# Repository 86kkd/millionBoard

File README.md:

# TODO list

- [x] 电源输入端大电容

- [x] 功率线宽度足够

- [x] 搞懂6pwm和3pwm控制的区别

- [ ] 模拟电路-数字电路去耦合

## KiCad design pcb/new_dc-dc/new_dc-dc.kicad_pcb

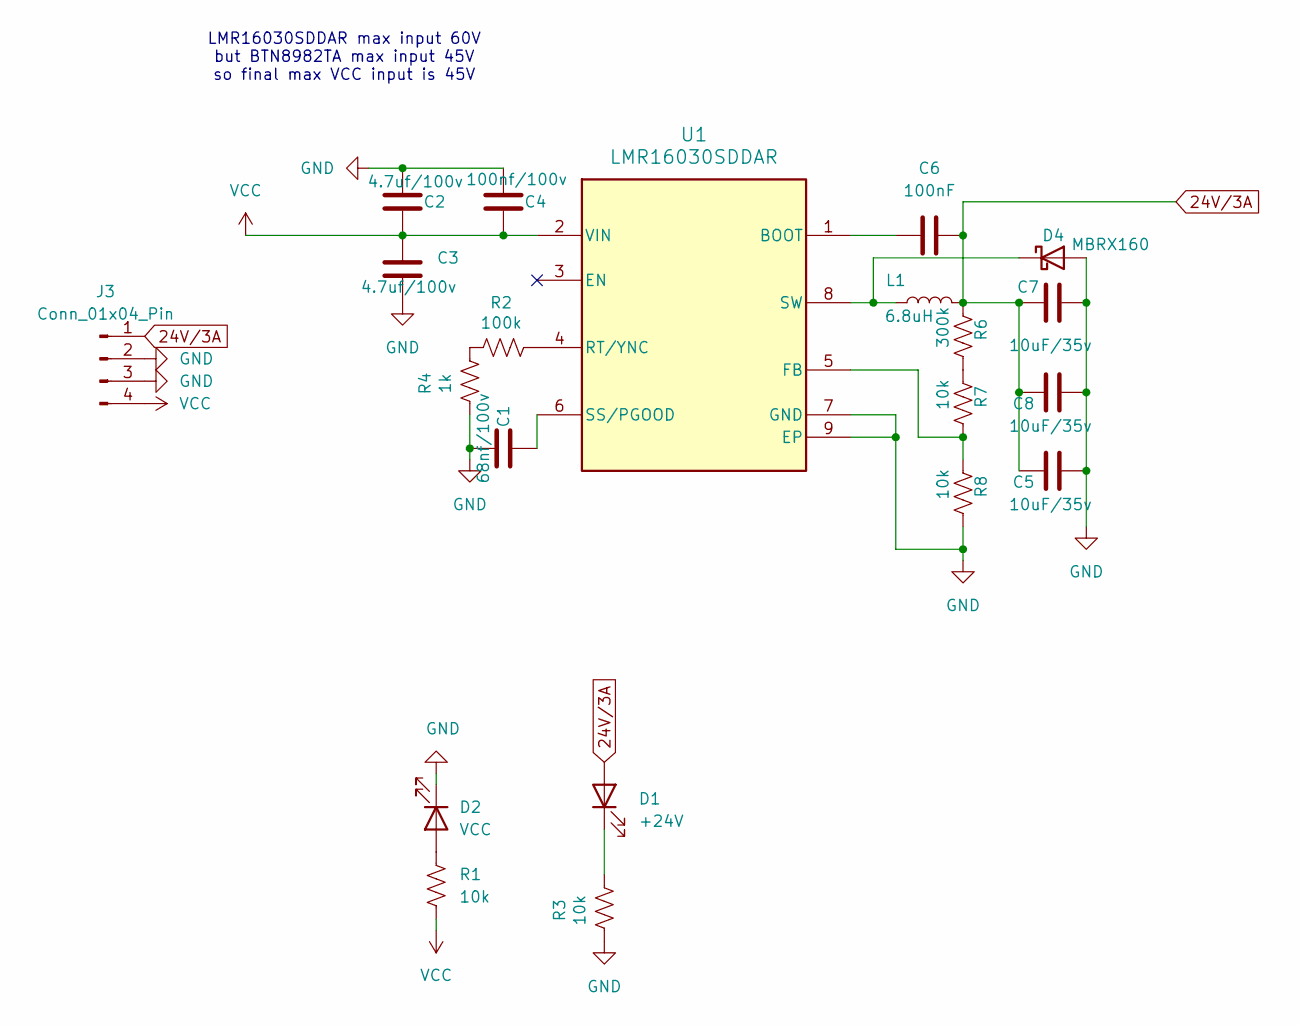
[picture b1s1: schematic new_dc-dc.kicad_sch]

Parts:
C1: 68nf/100v; C_0603_1608Metric
C2, C3: 4.7uf/100v; C_1210_3225Metric
C4: 100nf/100v; C_0603_1608Metric
C5, C7, C8: 10uF/35v; C_1210_3225Metric
C6: 100nF; C_0603_1608Metric
D1: +24V; LED_0603_1608Metric
D2: VCC; LED_0603_1608Metric
D4: MBRX160; D_SOD-123
J3: Conn_01x04_Pin
L1: 6.8uH; L_Chilisin_BMRA00040420
R1, R3, R7, R8: 10k; R_0603_1608Metric
R2: 100k; R_0603_1608Metric
R4: 1k; R_0603_1608Metric
R6: 300k; R_0603_1608Metric
U1: LMR16030SDDAR; TI_SO-PowerPAD-8_ThermalVias

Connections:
24V/3A: C5.2, C6.1, C7.1, C8.2, D1.2 (A), J3.1, L1.2, R6.1
GND: C1.2, C2.2, C3.2, C4.1, C5.1, C7.2, C8.1, D2.1 (K), D4.2 (A), J3.2, J3.3, R3.2, R4.2, R8.2, U1.7 (GND), U1.9 (EP)
unnamed: D1.1 (K), R3.1
unnamed: D2.2 (A), R1.2
unnamed: D4.1 (K), L1.1, U1.8 (SW)
unnamed: R2.2, R4.1
unnamed: R6.2, R7.1
unnamed: C6.2, U1.1 (BOOT)
unnamed: R7.2, R8.1, U1.5 (FB)
unnamed: R2.1, U1.4 (RT/YNC)
unnamed: C1.1, U1.6 (SS/PGOOD)
VCC: C2.1, C3.1, C4.2, J3.4, R1.1, U1.2 (VIN)

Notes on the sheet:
LMR16030SDDAR max input 60V but BTN8982TA max input 45V so final max VCC input is 45V

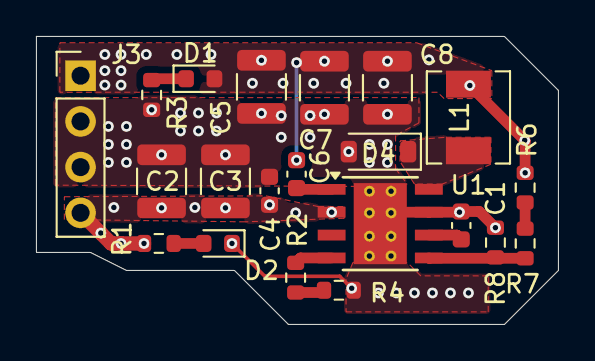
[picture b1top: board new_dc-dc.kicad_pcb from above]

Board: 6 copper layers, 29.0 x 16.0 mm, 21 parts (0 on the bottom side), 12 nets.

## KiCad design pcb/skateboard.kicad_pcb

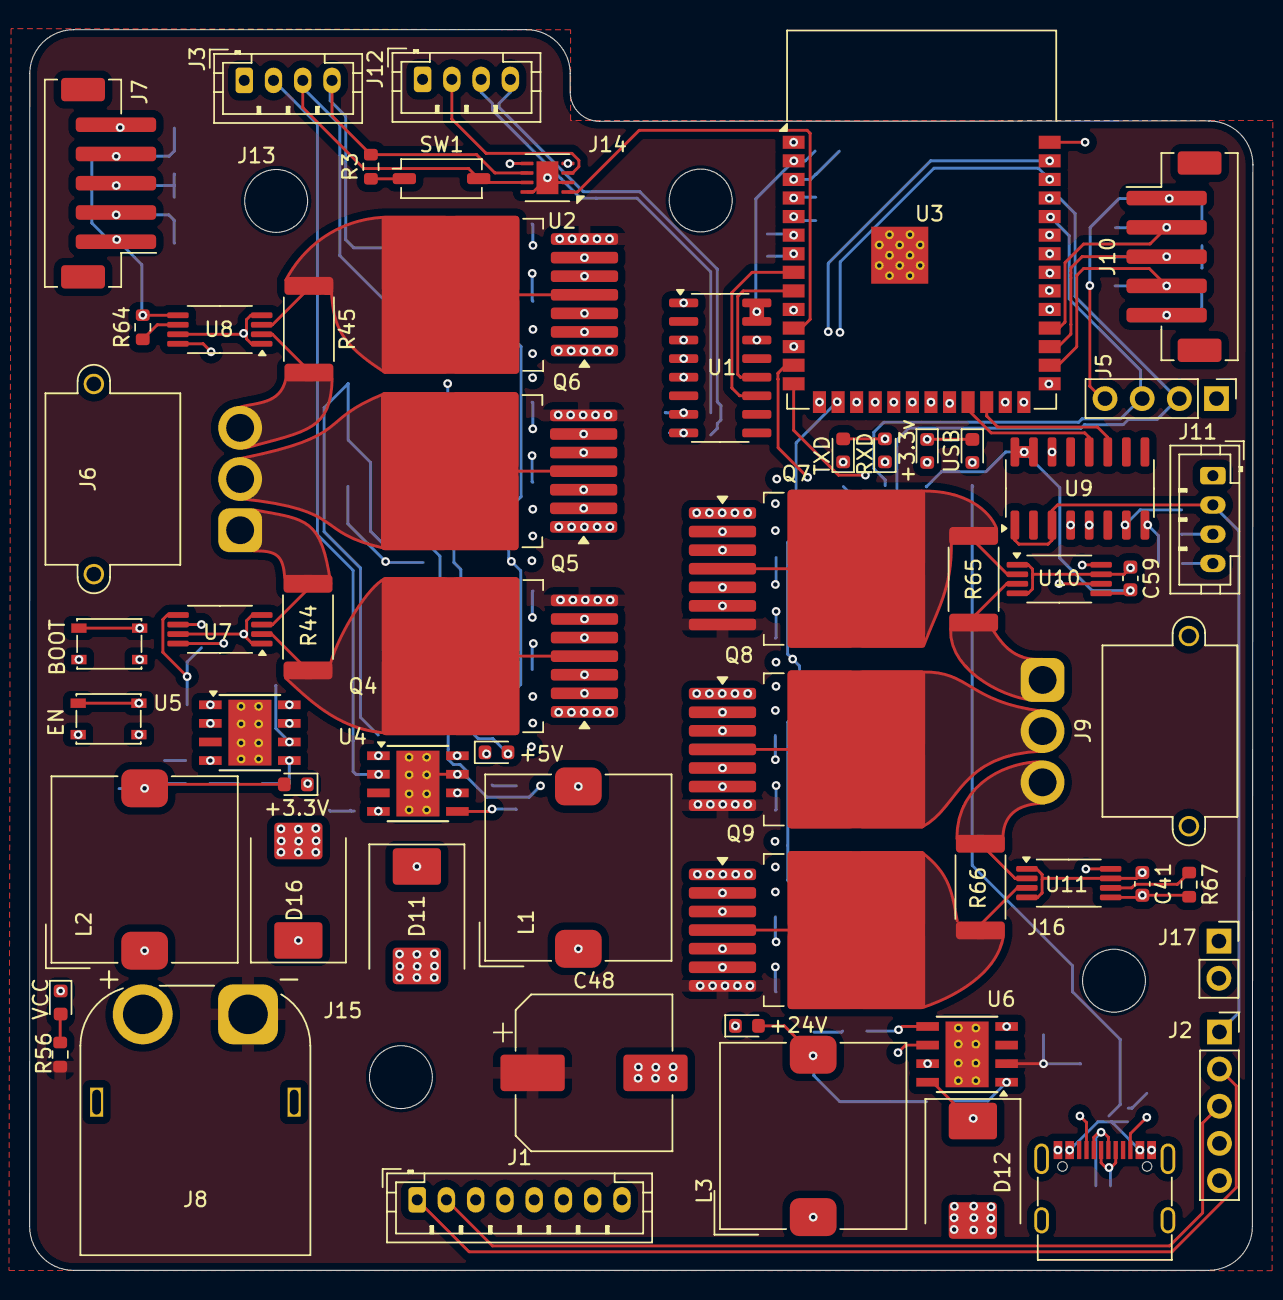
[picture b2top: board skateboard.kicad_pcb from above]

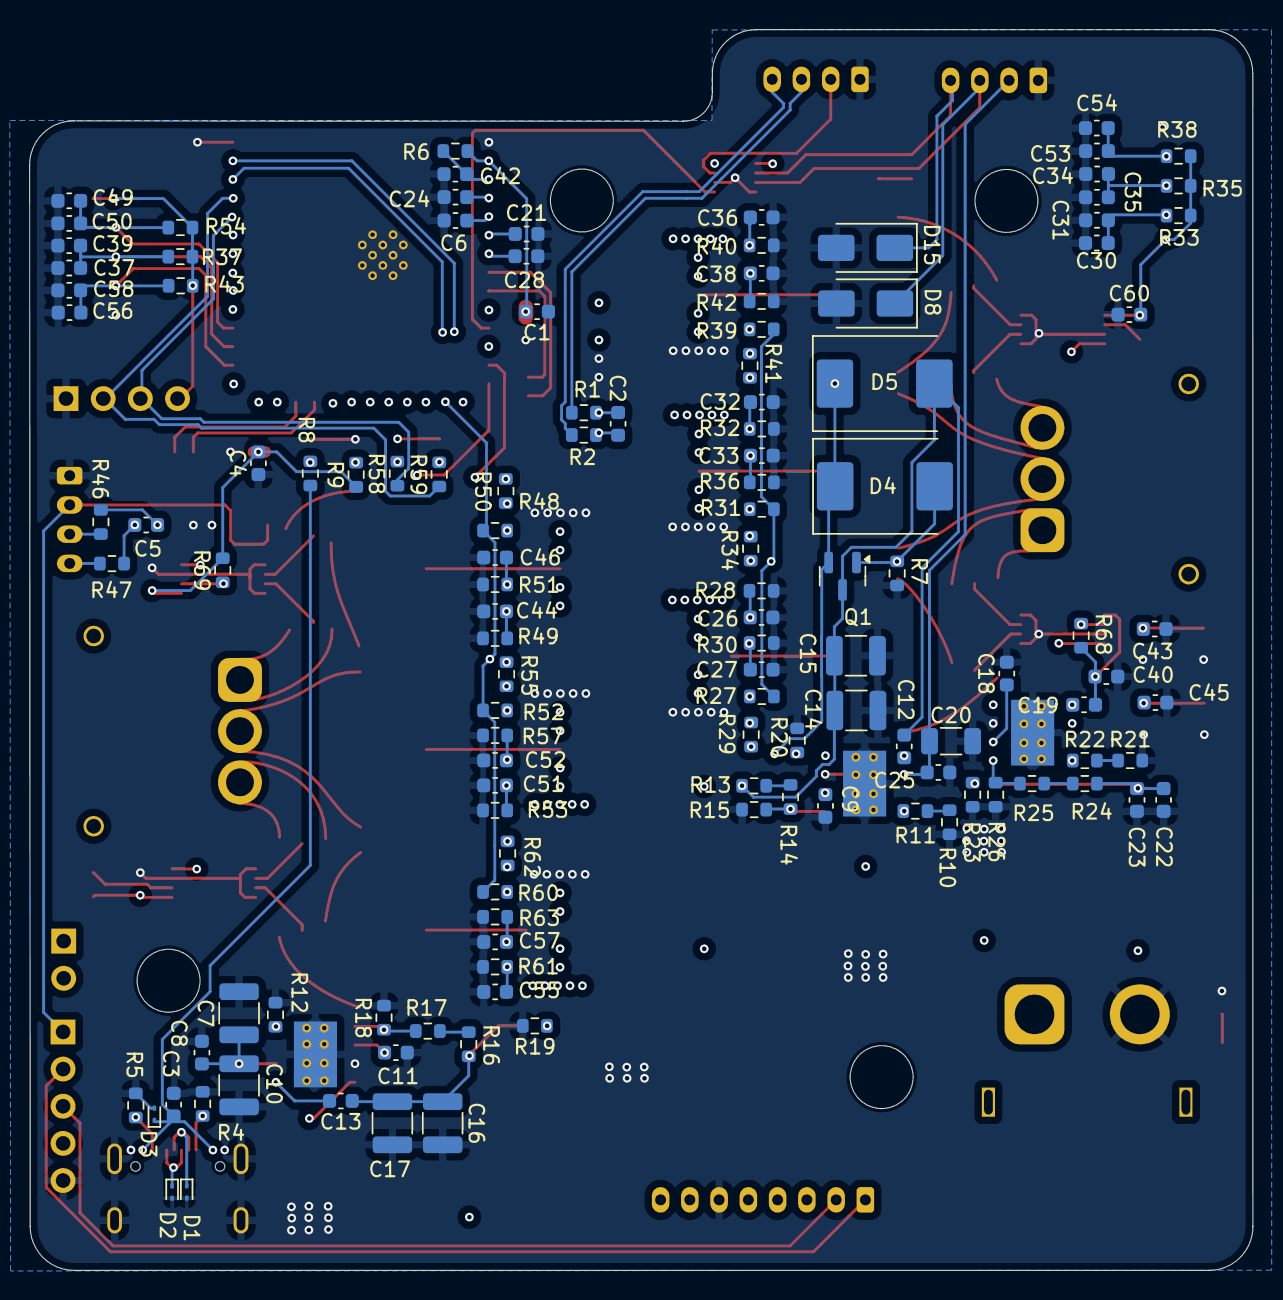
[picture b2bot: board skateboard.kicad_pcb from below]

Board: 4 copper layers, 83.6 x 84.8 mm, 186 parts (124 on the bottom side), 123 nets.

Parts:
3.3V4: VCC; LED_0603_1608Metric
C1, C4: 10uF; C_0603_1608Metric
C2, C5, C12, C13, C19, C27, C30, C33, C35, C38, C39, C40, C41, C46, C49, C52, C54, C57, C58, C59, C60: 100nF; C_0603_1608Metric
C3, C6, C8, C21, C24, C28: 100nf; C_0603_1608Metric
C7, C10: 10uf/50v; C_1210_3225Metric
C9, C18: 47nF; C_0603_1608Metric
C11: 68nF; C_0603_1608Metric
C14, C15: 10uF/16v; C_1210_3225Metric
C16, C17: 10uF/35v; C_1210_3225Metric
C20: 4.7uf/50v; C_1206_3216Metric
C22, C23: 10uF/10v; C_0603_1608Metric
C25: 100nf/50v; C_0603_1608Metric
C26, C32, C36, C44, C51, C55: 1nF; C_0603_1608Metric
C31, C34, C37, C50, C53, C56: 20pF; C_0603_1608Metric
C42, C43, C45: 1uF; C_0603_1608Metric
C48: 220uf; CP_Elec_10x10.5
D1, D2, D3: ESD9B5.0ST5G; D_SOD-923
D4, D5, D11, D12, D16: B560C; D_SMC
D6: USB; LED_0603_1608Metric
D7: +3.3v; LED_0603_1608Metric
D8, D15: SMAJ13CA; D_SMA
D9: RXD; LED_0603_1608Metric
D10: TXD; LED_0603_1608Metric
D13: +24V; LED_0603_1608Metric
D14: +5V; LED_0603_1608Metric
D17: +3.3V; LED_0603_1608Metric
J1: RC555; JST_PH_B8B-PH-K_1x08_P2.00mm_Vertical
J2: pa1010d; PinSocket_1x05_P2.54mm_Vertical
J3: can_sensor; JST_PH_B4B-PH-K_1x04_P2.00mm_Vertical
J4: USB_C_Receptacle_USB2.0_16P; USB_C_Receptacle_G-Switch_GT-USB-7010ASV
J5: UART; PinHeader_1x04_P2.54mm_Vertical
J6, J9: TB_MOTOR; AMASS_MR30PW-M_1x03_P3.50mm_Horizontal
J7, J10: PH_2.0; JST_PH_B5B-PH-SM4-TB_1x05-1MP_P2.00mm_Vertical
J8: power; AMASS_XT60PW-M_1x02_P7.20mm_Horizontal
J11: adc_sensor2; JST_PH_B4B-PH-K_1x04_P2.00mm_Vertical
J12: adc_sensor1; JST_PH_B4B-PH-K_1x04_P2.00mm_Vertical
J13, J14, J15, J16: Conn_01x01_Pin; MountingHole_4.3mm_M4
J17: Conn_01x02_Pin; PinSocket_1x02_P2.54mm_Vertical
L1: 47uH; L_TDK_SLF12565
L2: 10uH; L_TDK_SLF12565
L3: 22uH; L_TDK_SLF12565
Q1: AO3401A; SOT-23
Q4, Q5, Q6, Q7, Q8, Q9: BTN8982TA; TO-263-7_TabPin8
R1, R2, R46, R47: 100; R_0603_1608Metric
R3: 120; R_0603_1608Metric
R4, R5: 5K1; R_0603_1608Metric
R6, R8, R9, R58, R59: 10K; R_0603_1608Metric
R7, R15, R17, R18, R19, R20, R23, R26, R27, R29, R31, R34, R39, R41, R48, R50, R52, R55, R56, R60, R62: 10k; R_0603_1608Metric
R10, R21: 1.3k; R_0603_1608Metric
R11, R22: 62k; R_0603_1608Metric
R12: 100k; R_0603_1608Metric
R13: 56k; R_0603_1608Metric
R14: 680; R_0603_1608Metric
R16: 300k; R_0603_1608Metric
R24: 33k; R_0603_1608Metric
R25, R28, R32, R40, R49, R53, R61: 1k; R_0603_1608Metric
R30, R36, R42, R51, R57, R63: 0.51k; R_0603_1608Metric
R33, R35, R37, R38, R43, R54: 3.3k; R_0603_1608Metric
R44, R45, R65, R66: 0.001; R_2512_6332Metric
R64, R67, R68, R69: 200k; R_0603_1608Metric
SW1: SW_SPST; SW_DIP_SPSTx01_Slide_Copal_CHS-01A_W5.08mm_P1.27mm_JPin
SW2: BOOT; SW_SPST_PTS810
SW3: EN; SW_SPST_PTS810
U1, U9: HX711; SOP-16_3.9x9.9mm_P1.27mm
U2: SIT1042AQT/3; DFN-8-1EP_3x3mm_P0.65mm_EP1.5x2.25mm
U3: ESP32-S3-WROOM-1
U4, U5, U6: LMR16030SDDAR; TI_SO-PowerPAD-8_ThermalVias
U7, U8, U10, U11: INA240A2PW; TSSOP-8_4.4x3mm_P0.65mm

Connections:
24V/3A: C13.1, C16.1, C17.2, C20.2, C25.1, D13.2 (A), J3.2, L3.2, R16.1, U4.2 (VIN)
+3.3V: C1.2, C4.2, C19.1, C22.1, C23.2, C40.2, C41.2, C59.2, C60.2, D9.2 (A), D10.2 (A), D17.2 (A), J1.8, J5.4, J7.1, J10.1, L2.2, R6.1, R9.1, R24.1, R33.2, R35.2, R37.2, R38.2, R43.2, R54.2, R64.2, R67.2, R68.2, R69.2, U1.15 (RATE), U1.16 (DVDD), U2.5 (VIO), U3.2 (3V3), U7.5 (V+), U8.5 (V+), U9.15 (RATE), U9.16 (DVDD), U10.5 (V+), U11.5 (V+)
+5V: D4.1 (K), D5.1 (K), D14.2 (A), J2.1, J11.2, J12.2, Q1.2 (S), U1.1 (VSUP), U1.3 (AVDD), U2.3 (VCC), U5.2 (VIN), U9.1 (VSUP), U9.3 (AVDD)
/foc1/A0: C6.1, U3.5 (IO5), U7.8
/foc1/A1: C24.1, U3.4 (IO4), U8.8
/foc1/A2: C26.1, Q4.6 (IS), R28.1
/foc1/A3: C32.1, Q5.6 (IS), R32.1
/foc1/IN_1: R29.2, U3.19 (IO11)
/foc1/IN_2: R34.2, U3.18 (IO10)
/foc1/IN_3: R41.2, U3.17 (IO9)
/foc1/MOT_A: C30.1, C31.2, J7.2, R33.1, U3.31 (IO38)
/foc1/MOT_B: C34.2, C35.1, J7.3, R35.1, U3.34 (IO41)
/foc1/MOT_C: C53.2, C54.1, J7.4, R38.1, U3.35 (IO42)
/foc2/A0: C21.1, U3.6 (IO6), U10.8
/foc2/A1: C28.1, U3.7 (IO7), U11.8
/foc2/A2: C44.1, Q7.6 (IS), R49.1
/foc2/A3: C51.1, Q8.6 (IS), R53.1
/foc2/IN_1: R50.2, U3.22 (IO14)
/foc2/IN_2: R55.2, U3.21 (IO13)
/foc2/IN_3: R62.2, U3.20 (IO12)
/foc2/MOT_A: C49.1, C50.2, J10.2, R54.1, U3.30 (IO37)
/foc2/MOT_B: C37.2, C39.1, J10.3, R37.1, U3.29 (IO36)
/foc2/MOT_C: C56.2, C58.1, J10.4, R43.1, U3.28 (IO35)
/mcu/Battery_5V: C12.1, C14.1, C15.2, D5.2 (A), L1.2, Q1.3 (D), R13.1
Battery_RXD: J17.2, U3.25 (IO48)
Battery_TXD: J17.1, U3.26 (IO45)
CANH: D8.1 (A1), J3.3, SW1.2 (B), U2.7 (CANH)
CANL: D15.1 (A1), J3.4, R3.2, U2.6 (CANL)
DOUT_1: U1.12 (DOUT), U3.9 (IO16)
DOUT_2: U3.23 (IO21), U9.12 (DOUT)
EN: C42.1, C45.1, R6.2, SW3.1, U3.3 (EN)
GND: 3.3V4.1 (K), C1.1, C3.1, C4.1, C6.2, C7.2, C8.2, C9.2, C10.1, C11.2, C14.2, C15.1, C16.2, C17.1, C18.2, C20.1, C21.2, C22.2, C23.1, C24.2, C25.2, C26.2, C27.2, C28.2, C30.2, C31.1, C32.2, C33.2, C34.1, C35.2, C36.2, C37.1, C38.2, C39.2, C40.1, C41.1, C42.2, C43.2, C44.2, C45.2, C46.2, C48.2, C49.2, C50.1, C51.2, C52.2, C53.1, C54.2, C55.2, C56.1, C57.2, C58.2, C59.1, C60.1, D1.2 (A2), D2.2 (A2), D3.2 (A2), D6.1 (K), D7.1 (K), D8.2 (A2), D11.2 (A), D12.2 (A), D15.2 (A2), D16.2 (A), J1.6, J2.5, J3.1, J4.A1 (GND), J4.A12 (GND), J4.B1 (GND), J4.B12 (GND), J4.S1 (SHIELD), J5.1, J7.5, J8.2, J10.5, J11.1, J12.1, Q4.1, Q5.1, Q6.1, Q7.1, Q8.1, Q9.1, R4.1, R5.1, R7.2, R10.2, R12.2, R15.2, R18.2, R19.2, R20.2, R21.2, R23.2, R26.2, R28.2, R30.2, R32.2, R36.2, R40.2, R42.2, R49.2, R51.2, R53.2, R57.2, R61.2, R63.2, SW2.2, SW3.2, U1.4 (VFB), U1.5 (AGND), U1.14 (XI), U2.2 (GND), U2.8 (STB), U2.9 (EP), U3.1 (GND), U3.40 (GND), U3.41 (GND), U4.7 (GND), U4.9 (EP), U5.7 (GND), U5.9 (EP), U6.7 (GND), U6.9 (EP), U7.1 (GND), U7.4 (GND), U7.7 (REF1), U8.1 (GND), U8.4 (GND), U8.7 (REF1), U9.4 (VFB), U9.5 (AGND), U9.14 (XI), U10.1 (GND), U10.4 (GND), U10.7 (REF1), U11.1 (GND), U11.4 (GND), U11.7 (REF1)
INA1+: J12.4, R2.2
INA1-: J12.3, R1.2
INA2+: J11.4, R47.2
INA2-: J11.3, R46.2
IO0: C43.1, SW2.1, U3.27 (IO0)
IRQ: J1.5, U3.39 (IO1)
MISO: J1.4, U3.15 (IO3)
MOSI: J1.3, U3.12 (IO8)
MOTO_POWER: R27.2, R31.2, R39.2, R48.2, R52.2, R60.2, U3.16 (IO46)
unnamed: 3.3V4.2 (A), R56.2
unnamed: D6.2 (A), R8.2
unnamed: D7.2 (A), R9.2
unnamed: D9.1 (K), R58.2
unnamed: D10.1 (K), R59.2
unnamed: D11.1 (K), L1.1, U4.8 (SW)
unnamed: D12.1 (K), L3.1, U6.8 (SW)
unnamed: D13.1 (K), R19.1
unnamed: D14.1 (K), R20.1
unnamed: D16.1 (K), L2.1, U5.8 (SW)
unnamed: D17.1 (K), R23.1
unnamed: J4.A5 (CC1), R4.2
unnamed: J4.B5 (CC2), R5.2
unnamed: J6.1, R44.1, U7.3 (-)
unnamed: J6.2, Q5.4, Q5.8
unnamed: J6.3, R45.2, U8.2 (+)
unnamed: J9.1, R65.1, U10.3 (-)
unnamed: J9.2, Q8.4, Q8.8
unnamed: J9.3, R66.2, U11.2 (+)
unnamed: Q4.2 (IN), R29.1
unnamed: Q4.3 (INH), R27.1
unnamed: C27.1, Q4.5 (SR), R30.1
unnamed: Q5.2 (IN), R34.1
unnamed: Q5.3 (INH), R31.1
unnamed: C33.1, Q5.5 (SR), R36.1
unnamed: Q6.2 (IN), R41.1
unnamed: Q6.3 (INH), R39.1
unnamed: C36.1, Q6.6 (IS), R40.1
unnamed: C38.1, Q6.5 (SR), R42.1
unnamed: Q7.2 (IN), R50.1
unnamed: Q7.3 (INH), R48.1
unnamed: C46.1, Q7.5 (SR), R51.1
unnamed: Q8.2 (IN), R55.1
unnamed: Q8.3 (INH), R52.1
unnamed: C52.1, Q8.5 (SR), R57.1
unnamed: Q9.2 (IN), R62.1
unnamed: Q9.3 (INH), R60.1
unnamed: C55.1, Q9.6 (IS), R61.1
unnamed: C57.1, Q9.5 (SR), R63.1
unnamed: R10.1, R11.2
unnamed: R13.2, R14.1
unnamed: R16.2, R17.1
unnamed: R21.1, R22.2
unnamed: R24.2, R25.1
unnamed: R3.1, SW1.1 (A)
unnamed: C2.1, R2.1, U1.8 (INA+)
unnamed: C2.2, R1.1, U1.7 (INA-)
unnamed: C12.2, U4.1 (BOOT)
unnamed: R14.2, R15.1, U4.5 (FB)
unnamed: R11.1, U4.4 (RT/YNC)
unnamed: C9.1, U4.6 (SS/PGOOD)
unnamed: C19.2, U5.1 (BOOT)
unnamed: R25.2, R26.1, U5.5 (FB)
unnamed: R22.1, U5.4 (RT/YNC)
unnamed: C18.1, U5.6 (SS/PGOOD)
unnamed: C13.2, U6.1 (BOOT)
unnamed: R17.2, R18.1, U6.5 (FB)
unnamed: R12.1, U6.4 (RT/YNC)
unnamed: C11.1, U6.6 (SS/PGOOD)
unnamed: Q4.4, Q4.8, R44.2, U7.2 (+)
unnamed: R68.1, U7.6 (REF2)
unnamed: Q6.4, Q6.8, R45.1, U8.3 (-)
unnamed: R64.1, U8.6 (REF2)
unnamed: C5.1, R47.1, U9.8 (INA+)
unnamed: C5.2, R46.1, U9.7 (INA-)
unnamed: Q7.4, Q7.8, R65.2, U10.2 (+)
unnamed: R69.1, U10.6 (REF2)
unnamed: Q9.4, Q9.8, R66.1, U11.3 (-)
unnamed: R67.1, U11.6 (REF2)
PD_SCK1: U1.11 (PD_SCK), U3.8 (IO15)
PD_SCK2: U3.24 (IO47), U9.11 (PD_SCK)
RST: J1.7, U3.38 (IO2)
RXD_SENSOR: U2.4 (RXD), U3.10 (IO17)
SCK: J1.2, J2.3, U3.33 (IO40)
SDA: J1.1, J2.2, U3.32 (IO39)
TXD_SENSOR: U2.1 (TXD), U3.11 (IO18)
U0_RXD: J5.3, R58.1, U3.36 (RXD0)
U0_TXD: J5.2, R59.1, U3.37 (TXD0)
USB_D+: D2.1 (A1), J4.A6 (D+), J4.B6 (D+), U3.14 (USB_D+)
USB_D-: D1.1 (A1), J4.A7 (D-), J4.B7 (D-), U3.13 (USB_D-)
VBUS: C3.2, D3.1 (A1), D4.2 (A), J4.A4 (VBUS), J4.A9 (VBUS), J4.B4 (VBUS), J4.B9 (VBUS), Q1.1 (G), R7.1, R8.1
VCC: C7.1, C8.1, C10.2, C48.1, J8.1, Q4.7, Q5.7, Q6.7, Q7.7, Q8.7, Q9.7, R56.1, U6.2 (VIN)

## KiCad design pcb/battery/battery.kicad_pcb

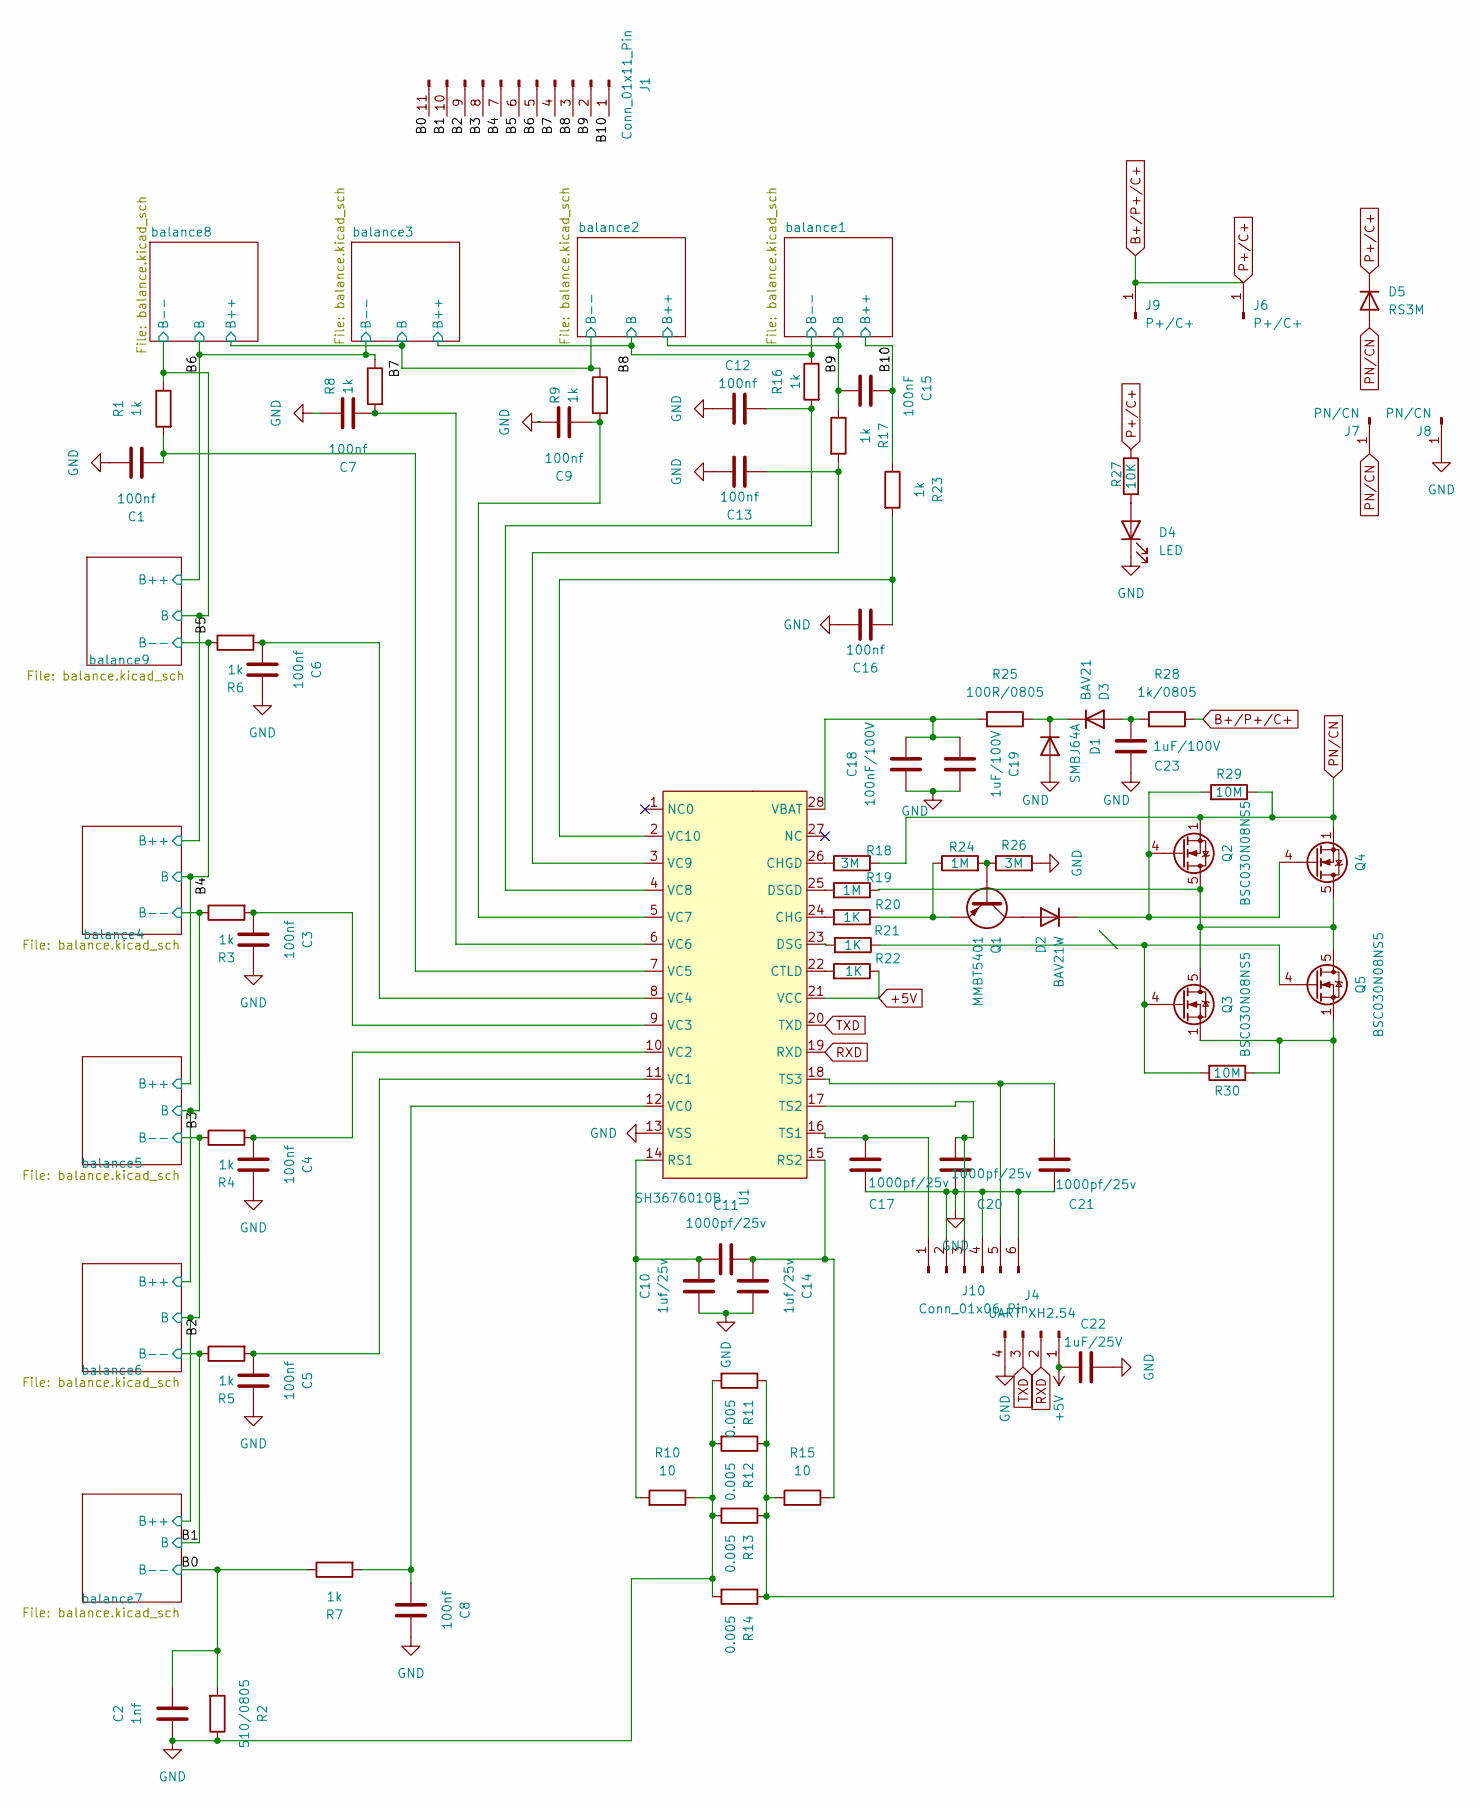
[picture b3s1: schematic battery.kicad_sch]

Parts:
C1, C3, C4, C5, C6, C7, C8, C9, C12, C13, C16: 100nf; C_0603_1608Metric
C2: 1nf; C_0603_1608Metric
C10, C14: 1uf/25v; C_0603_1608Metric
C11, C17, C20, C21: 1000pf/25v; C_0603_1608Metric
C15: 100nF; C_0603_1608Metric
C18: 100nF/100V; C_0603_1608Metric
C19, C23: 1uF/100V; C_0603_1608Metric
C22: 1uF/25V; C_0603_1608Metric
D1: SMBJ64A; D_SMB-SMC_Universal_Handsoldering
D2: BAV21W; D_SOD-123
D3: BAV21; D_SOD-123
D4: LED; LED_0603_1608Metric
D5: RS3M; D_SMB-SMC_Universal_Handsoldering
J1: Conn_01x11_Pin; JST_PH_B11B-PH-K_1x11_P2.00mm_Vertical
J4: UART XH2.54; PinHeader_1x04_P2.54mm_Vertical
J6, J9: P+/C+; MountingHole_2.2mm_M2_DIN965_Pad_TopBottom
J7, J8: PN/CN; MountingHole_2.2mm_M2_DIN965_Pad_TopBottom
J10: Conn_01x06_Pin; JST_PH_B6B-PH-K_1x06_P2.00mm_Vertical
Q1: MMBT5401; SOT-23
Q2, Q3, Q4, Q5: BSC030N08NS5; TDSON-8-1
R1, R3, R4, R5, R6, R7, R8, R9, R16, R17, R23: 1k; R_0603_1608Metric
R2: 510/0805; R_0805_2012Metric
R10, R15: 10; R_0603_1608Metric
R11, R12, R13, R14: 0.005; R_2512_6332Metric
R18, R26: 3M; R_0603_1608Metric
R19, R24: 1M; R_0603_1608Metric
R20, R21, R22: 1K; R_0603_1608Metric
R25: 100R/0805; R_0805_2012Metric
R27: 10K; R_0603_1608Metric
R28: 1k/0805; R_0805_2012Metric
R29, R30: 10M; R_0603_1608Metric
U1: SH3676010B; TSSOP-28_4.4x9.7mm_P0.65mm

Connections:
+5V: C22.1, J4.1, R22.1, U1.21 (VCC)
/B0: C2.2, J1.11, R2.2, R7.1; also elsewhere on the board
/B1: J1.10, R5.1; also elsewhere on the board
/B2: J1.9, R4.1; also elsewhere on the board
/B3: J1.8, R3.1; also elsewhere on the board
/B4: J1.7, R6.1; also elsewhere on the board
/B5: J1.6, R1.1; also elsewhere on the board
/B6: J1.5, R8.1; also elsewhere on the board
/B7: J1.4, R9.1; also elsewhere on the board
/B8: J1.3, R16.1; also elsewhere on the board
/B9: C15.2, J1.2, R17.1; also elsewhere on the board
/B10: C15.1, J1.1, R23.1; also elsewhere on the board
B+/P+/C+: D5.1 (K), J6.1, J9.1, R27.1, R28.1
GND: C1.1, C2.1, C3.1, C4.1, C5.1, C6.1, C7.1, C8.1, C9.1, C10.1, C12.1, C13.2, C14.1, C16.2, C17.2, C18.2, C19.1, C20.2, C21.2, C22.2, C23.1, D1.2 (A), D4.1 (K), J4.4, J8.1, J10.2, J10.4, J10.6, R2.1, R10.1, R11.2, R12.2, R13.2, R14.2, R26.2, U1.13 (VSS)
unnamed: D1.1 (K), D3.1 (K), R25.1
unnamed: D2.2 (A), Q1.3 (C)
unnamed: D2.1 (K), Q2.4 (G), Q4.4 (G), R29.2
unnamed: C23.2, D3.2 (A), R28.2
unnamed: D4.2 (A), R27.2
unnamed: C17.1, J10.1, U1.16 (TS1)
unnamed: C20.1, J10.3, U1.17 (TS2)
unnamed: C21.1, J10.5, U1.18 (TS3)
unnamed: Q1.1 (B), R24.2, R26.1
unnamed: Q1.2 (E), R20.1, R24.1
unnamed: Q2.5 (D), Q3.5 (D), Q4.5 (D), Q5.5 (D), R19.1
unnamed: Q3.4 (G), Q5.4 (G), R21.1, R30.2
unnamed: Q3.1 (S), Q3.2 (S), Q3.3 (S), Q5.1 (S), Q5.2 (S), Q5.3 (S), R11.1, R12.1, R13.1, R14.1, R15.2, R30.1
unnamed: R20.2, U1.24 (CHG)
unnamed: R18.2, U1.26 (CHGD)
unnamed: R22.2, U1.22 (CTLD)
unnamed: R21.2, U1.23 (DSG)
unnamed: R19.2, U1.25 (DSGD)
unnamed: C10.2, C11.2, R10.2, U1.14 (RS1)
unnamed: C11.1, C14.2, R15.1, U1.15 (RS2)
unnamed: C18.1, C19.2, R25.2, U1.28 (VBAT)
unnamed: C8.2, R7.2, U1.12 (VC0)
unnamed: C5.2, R5.2, U1.11 (VC1)
unnamed: C4.2, R4.2, U1.10 (VC2)
unnamed: C3.2, R3.2, U1.9 (VC3)
unnamed: C6.2, R6.2, U1.8 (VC4)
unnamed: C1.2, R1.2, U1.7 (VC5)
unnamed: C7.2, R8.2, U1.6 (VC6)
unnamed: C9.2, R9.2, U1.5 (VC7)
unnamed: C12.2, R16.2, U1.4 (VC8)
unnamed: C13.1, R17.2, U1.3 (VC9)
unnamed: C16.1, R23.2, U1.2 (VC10)
PN/CN: D5.2 (A), J7.1, Q2.1 (S), Q2.2 (S), Q2.3 (S), Q4.1 (S), Q4.2 (S), Q4.3 (S), R18.1, R29.1
RXD: J4.2, U1.19 (RXD)
TXD: J4.3, U1.20 (TXD)

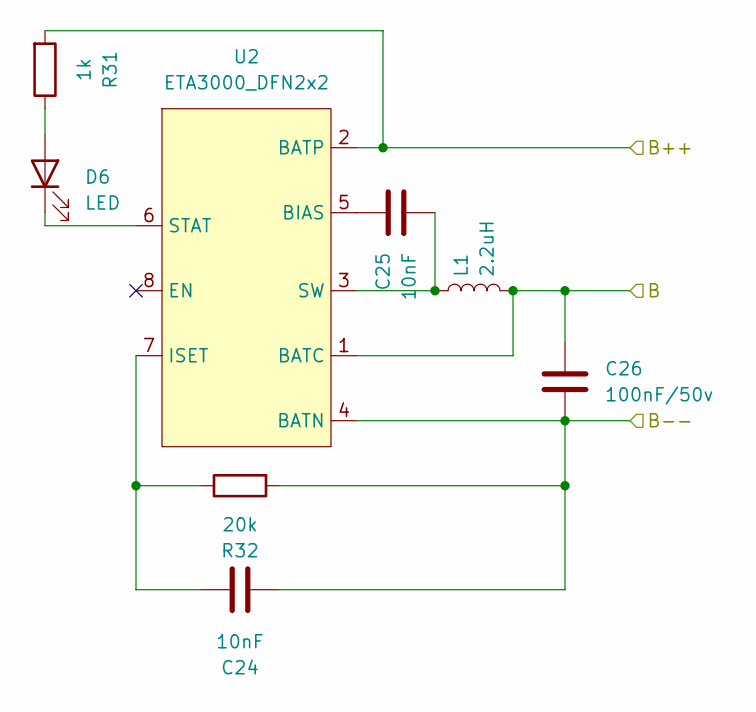
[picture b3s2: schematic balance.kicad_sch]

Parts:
C24, C25: 10nF; C_0603_1608Metric
C26: 100nF/50v; C_0603_1608Metric
D6: LED; LED_0603_1608Metric
L1: 2.2uH; L_Neosid_Ms42
R31: 1k; R_0603_1608Metric
R32: 20k; R_0603_1608Metric
U2: ETA3000_DFN2x2; DFN-8_2x2mm_P0.5mm

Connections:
/B8: C24.2, C26.2, R32.2, U2.4 (BATN); also elsewhere on the board
/B9: C26.1, L1.2, U2.1 (BATC); also elsewhere on the board
/B10: R31.2, U2.2 (BATP); also elsewhere on the board
unnamed: D6.2 (A), R31.1
unnamed: D6.1 (K), U2.6 (STAT)
unnamed: C25.1, U2.5 (BIAS)
unnamed: C24.1, R32.1, U2.7 (ISET)
unnamed: C25.2, L1.1, U2.3 (SW)

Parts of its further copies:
C27, C28, C30, C31, C33, C34, C36, C37, C39, C40, C42, C43, C45, C46, C48, C49: 10nF; C_0603_1608Metric
C29, C32, C35, C38, C41, C44, C47, C50: 100nF/50v; C_0603_1608Metric
D7, D8, D9, D10, D11, D12, D13, D14: LED; LED_0603_1608Metric
L2, L3, L4, L5, L6, L7, L8, L9: 2.2uH; L_Neosid_Ms42
R33, R35, R37, R39, R41, R43, R45, R47: 1k; R_0603_1608Metric
R34, R36, R38, R40, R42, R44, R46, R48: 20k; R_0603_1608Metric
U3, U4, U5, U6, U7, U8, U9, U10: ETA3000_DFN2x2; DFN-8_2x2mm_P0.5mm

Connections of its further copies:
/B0: C42.2, C44.2, R44.2, U8.4 (BATN); also elsewhere on the board
/B1: C39.2, C41.2, C44.1, L7.2, R42.2, U7.4 (BATN), U8.1 (BATC); also elsewhere on the board
/B2: C36.2, C38.2, C41.1, L6.2, R40.2, R43.2, U6.4 (BATN), U7.1 (BATC), U8.2 (BATP); also elsewhere on the board
/B3: C33.2, C35.2, C38.1, L5.2, R38.2, R41.2, U5.4 (BATN), U6.1 (BATC), U7.2 (BATP); also elsewhere on the board
/B4: C35.1, C48.2, C50.2, L4.2, R39.2, R48.2, U5.1 (BATC), U6.2 (BATP), U10.4 (BATN); also elsewhere on the board
/B5: C45.2, C47.2, C50.1, L9.2, R37.2, R46.2, U5.2 (BATP), U9.4 (BATN), U10.1 (BATC); also elsewhere on the board
/B6: C30.2, C32.2, C47.1, L8.2, R36.2, R47.2, U4.4 (BATN), U9.1 (BATC), U10.2 (BATP); also elsewhere on the board
/B7: C27.2, C29.2, C32.1, L3.2, R34.2, R45.2, U3.4 (BATN), U4.1 (BATC), U9.2 (BATP); also elsewhere on the board
/B8: C29.1, L2.2, R35.2, U3.1 (BATC), U4.2 (BATP); also elsewhere on the board
/B9: R33.2, U3.2 (BATP); also elsewhere on the board
unnamed: D7.2 (A), R33.1
unnamed: D7.1 (K), U3.6 (STAT)
unnamed: D8.2 (A), R35.1
unnamed: D8.1 (K), U4.6 (STAT)
unnamed: D9.2 (A), R37.1
unnamed: D9.1 (K), U5.6 (STAT)
unnamed: D10.2 (A), R39.1
unnamed: D10.1 (K), U6.6 (STAT)
unnamed: D11.2 (A), R41.1
unnamed: D11.1 (K), U7.6 (STAT)
unnamed: D12.2 (A), R43.1
unnamed: D12.1 (K), U8.6 (STAT)
unnamed: D13.2 (A), R45.1
unnamed: D13.1 (K), U9.6 (STAT)
unnamed: D14.2 (A), R47.1
unnamed: D14.1 (K), U10.6 (STAT)
unnamed: C28.1, U3.5 (BIAS)
unnamed: C27.1, R34.1, U3.7 (ISET)
unnamed: C28.2, L2.1, U3.3 (SW)
unnamed: C31.1, U4.5 (BIAS)
unnamed: C30.1, R36.1, U4.7 (ISET)
unnamed: C31.2, L3.1, U4.3 (SW)
unnamed: C34.1, U5.5 (BIAS)
unnamed: C33.1, R38.1, U5.7 (ISET)
unnamed: C34.2, L4.1, U5.3 (SW)
unnamed: C37.1, U6.5 (BIAS)
unnamed: C36.1, R40.1, U6.7 (ISET)
unnamed: C37.2, L5.1, U6.3 (SW)
unnamed: C40.1, U7.5 (BIAS)
unnamed: C39.1, R42.1, U7.7 (ISET)
unnamed: C40.2, L6.1, U7.3 (SW)
unnamed: C43.1, U8.5 (BIAS)
unnamed: C42.1, R44.1, U8.7 (ISET)
unnamed: C43.2, L7.1, U8.3 (SW)
unnamed: C46.1, U9.5 (BIAS)
unnamed: C45.1, R46.1, U9.7 (ISET)
unnamed: C46.2, L8.1, U9.3 (SW)
unnamed: C49.1, U10.5 (BIAS)
unnamed: C48.1, R48.1, U10.7 (ISET)
unnamed: C49.2, L9.1, U10.3 (SW)

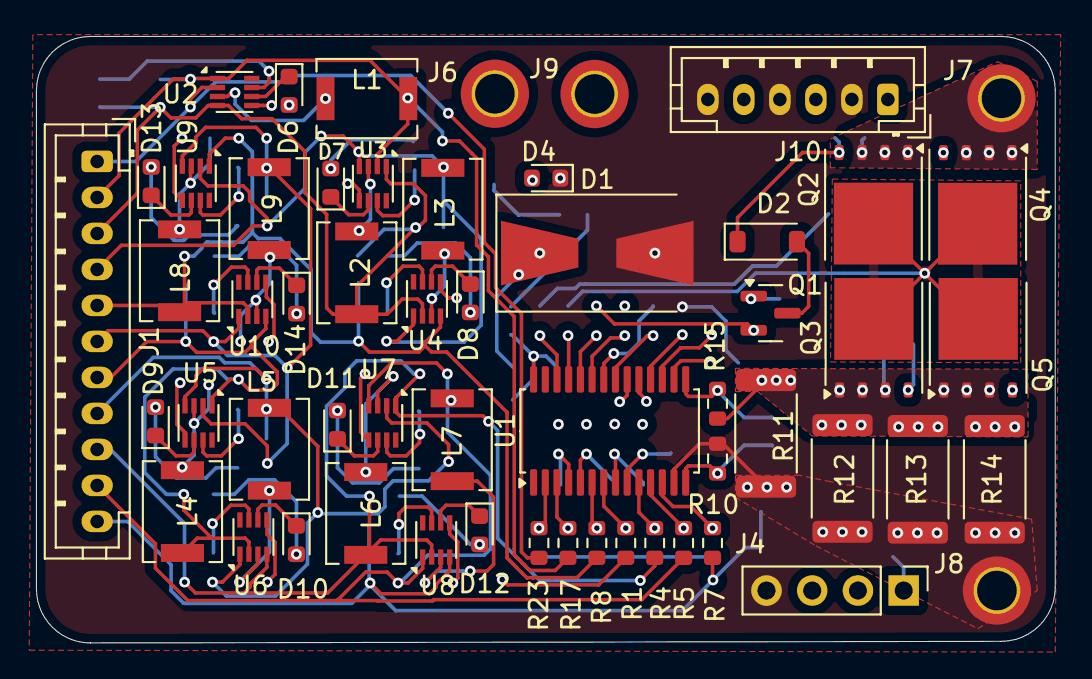
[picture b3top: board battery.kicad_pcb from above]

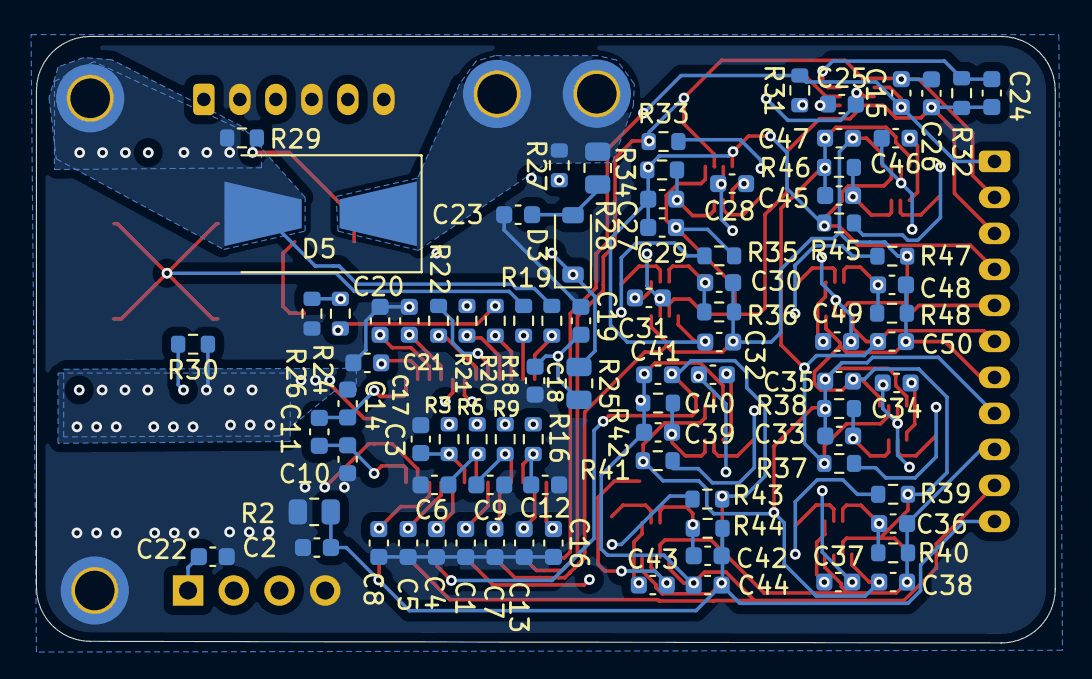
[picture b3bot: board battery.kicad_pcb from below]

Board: 6 copper layers, 56.6 x 33.7 mm, 143 parts (87 on the bottom side), 94 nets.

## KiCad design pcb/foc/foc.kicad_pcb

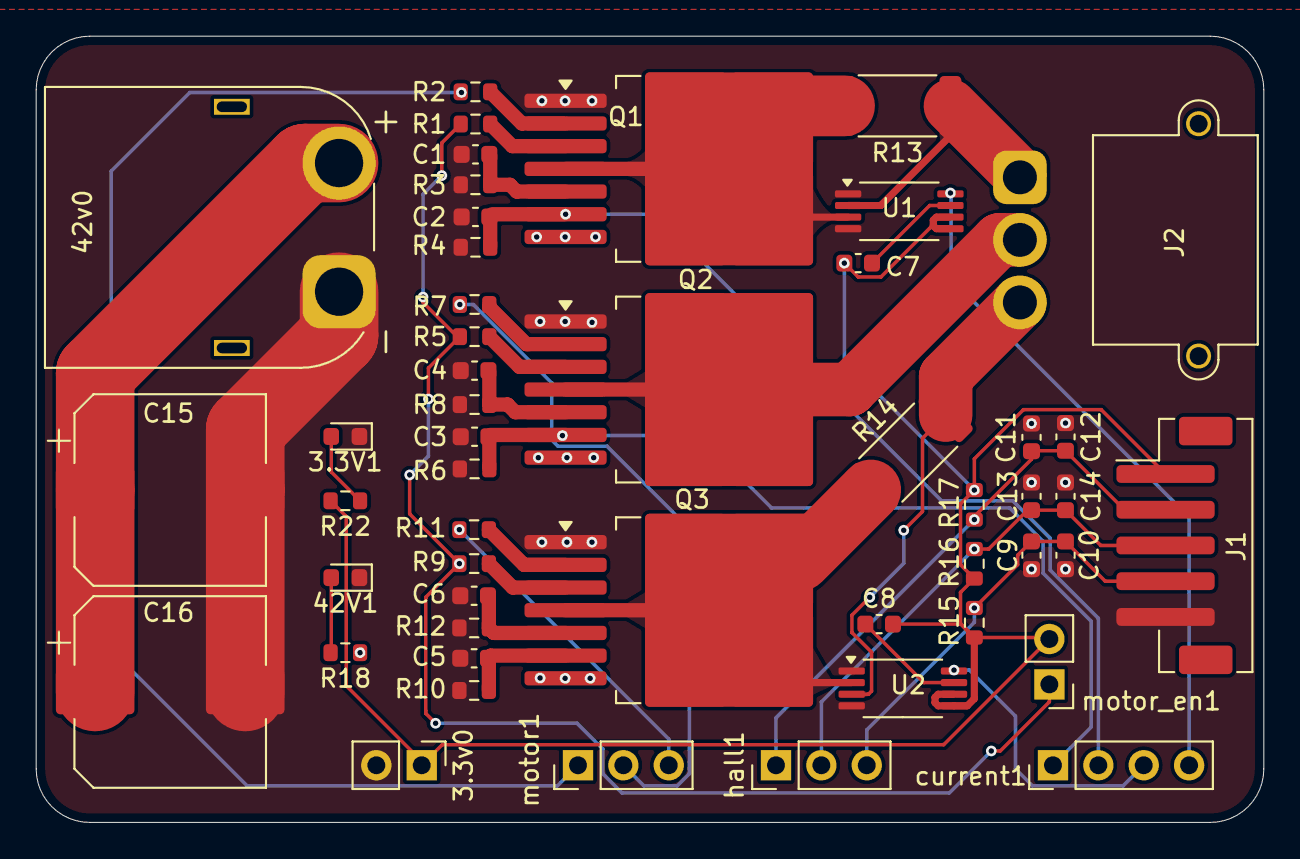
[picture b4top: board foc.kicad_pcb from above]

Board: 2 copper layers, 68.7 x 44.0 mm, 50 parts (0 on the bottom side), 33 nets.

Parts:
3.3V1, 42V1: LED; LED_0603_1608Metric
3.3v0: Power3.3; PinHeader_1x02_P2.54mm_Vertical
42v0: Power42V; AMASS_XT60PW-M_1x02_P7.20mm_Horizontal
C1, C4, C6, C9, C11, C13: 100nF; C_0603_1608Metric
C2, C3, C5: 1nF; C_0603_1608Metric
C7, C8: 0.1nF; C_0603_1608Metric
C10, C12, C14: 20pF; C_0603_1608Metric
C15, C16: 330uf; CP_Elec_10x10.5
J1: PH_2.0; JST_PH_B5B-PH-SM4-TB_1x05-1MP_P2.00mm_Vertical
J2: TB_MOTOR; AMASS_MR30PW-M_1x03_P3.50mm_Horizontal
Q1, Q2, Q3: BTN8982TA; TO-263-7_TabPin8
R1, R2, R5, R7, R9, R11, R18: 10k; R_0603_1608Metric
R3, R8, R12: 0.51k; R_0603_1608Metric
R4, R6, R10, R22: 1k; R_0603_1608Metric
R13, R14: 0.001; R_2512_6332Metric
R15, R16, R17: 3.3k; R_0603_1608Metric
U1, U2: INA240A2PW; TSSOP-8_4.4x3mm_P0.65mm
current1: current info; PinHeader_1x04_P2.54mm_Vertical
hall1: sig; PinHeader_1x03_P2.54mm_Vertical
motor1: input; PinHeader_1x03_P2.54mm_Vertical
motor_en1: en_sig; PinHeader_1x02_P2.54mm_Vertical

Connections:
+3.3V: 3.3v0.1, C7.2, C8.2, J1.1, R15.2, R16.2, R17.1, R22.2, U1.5 (V+), U1.6 (REF2), U2.5 (V+), U2.6 (REF2), motor_en1.2
A0: U1.8, current1.4
A1: U2.8, current1.3
A2: C2.1, Q1.6 (IS), R4.1, current1.2
A3: C3.1, Q2.6 (IS), R6.1, current1.1
GND: 3.3V1.1 (K), 3.3v0.2, 42V1.1 (K), 42v0.1, C1.2, C2.2, C3.2, C4.2, C5.2, C6.2, C9.2, C10.1, C11.2, C12.1, C13.2, C14.1, C15.2, C16.2, J1.5, Q1.1, Q2.1, Q3.1, R3.2, R4.2, R6.2, R8.2, R10.2, R12.2, U1.1 (GND), U1.4 (GND), U2.1 (GND), U2.4 (GND)
INH_EN: R1.2, R5.2, R9.2, motor_en1.1
IN_1: R2.2, motor1.1
IN_2: R7.2, motor1.2
IN_3: R11.2, motor1.3
MOT_A: C11.1, C12.2, J1.2, R17.2, hall1.1
MOT_B: C13.1, C14.2, J1.3, R16.1, hall1.2
MOT_C: C9.1, C10.2, J1.4, R15.1, hall1.3
unnamed: 3.3V1.2 (A), R22.1
unnamed: 42V1.2 (A), R18.2
unnamed: Q1.2 (IN), R2.1
unnamed: Q1.3 (INH), R1.1
unnamed: C1.1, Q1.5 (SR), R3.1
unnamed: Q2.2 (IN), R7.1
unnamed: Q2.3 (INH), R5.1
unnamed: C4.1, Q2.5 (SR), R8.1
unnamed: Q3.2 (IN), R11.1
unnamed: Q3.3 (INH), R9.1
unnamed: C5.1, Q3.6 (IS), R10.1
unnamed: C6.1, Q3.5 (SR), R12.1
unnamed: C7.1, U1.7 (REF1)
unnamed: C8.1, U2.7 (REF1)
VCC: 42v0.2, C15.1, C16.1, Q1.7, Q2.7, Q3.7, R18.1
out1: J2.1, R13.1, U1.2 (+)
out1_cs: Q1.4, Q1.8, R13.2, U1.3 (-)
out2: J2.2, Q2.4, Q2.8
out3: J2.3, R14.2, U2.3 (-)
out3_cs: Q3.4, Q3.8, R14.1, U2.2 (+)
